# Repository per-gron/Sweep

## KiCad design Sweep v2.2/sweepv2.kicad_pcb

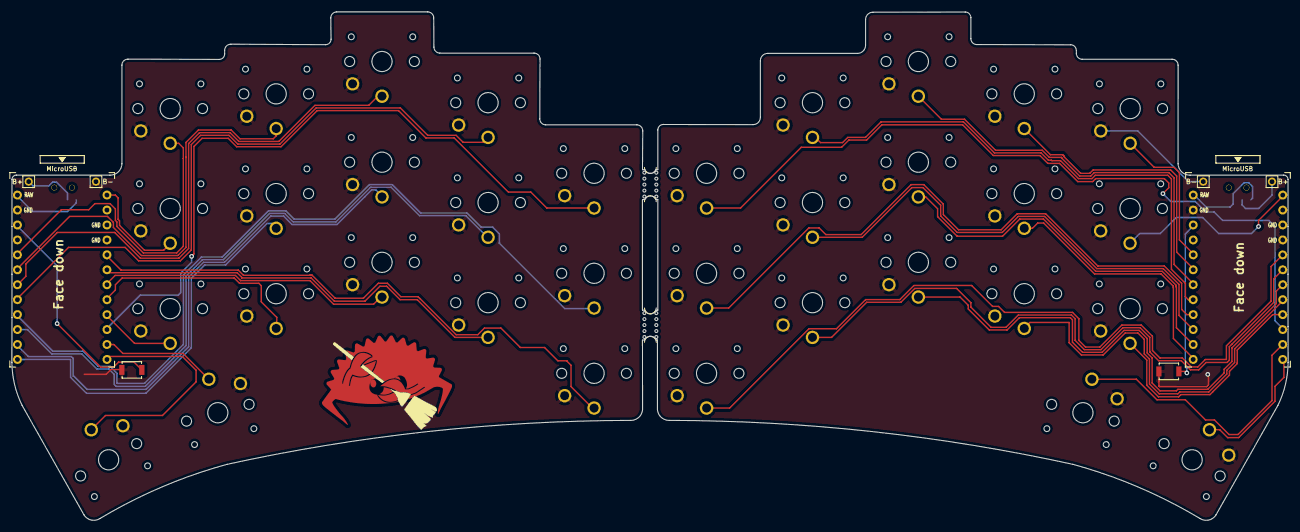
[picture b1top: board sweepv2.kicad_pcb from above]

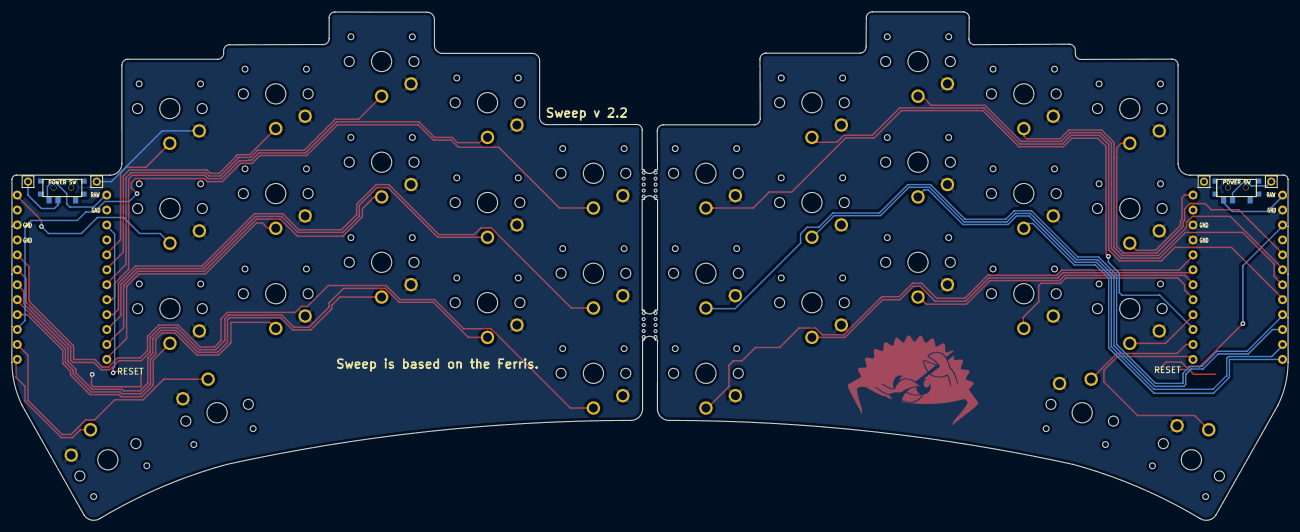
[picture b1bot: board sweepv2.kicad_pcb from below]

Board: 2 copper layers, 216.9 x 86.4 mm, 46 parts (2 on the bottom side), 41 nets.

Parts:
B+: MountingHole_Pad; 1pin_conn
B+#2: MountingHole_Pad; 1pin_conn
B-: MountingHole_Pad; 1pin_conn
B-#2: MountingHole_Pad; 1pin_conn
POWER SW: SW_SPDT; SPDT_C128955
POWER SW#2: SW_SPDT; SPDT_C128955
RSW1, RSW2: SW_Push; SW_SPST_B3U-1000P
SW2, SW2_r1, SW3, SW3_r1, SW4, SW4_r1, SW5, SW5_r1, SW6, SW6_r1, SW7_r1, SW8, SW8_r1, SW9, SW9_r1, SW10, SW11, SW11_r1, SW12, SW12_r1, SW13_r1, SW14, SW15, SW15_r1, SW16, SW16_r1, SW17, SW17_r1, SW18, SW18_r1, SW20, SW20_r1, SW21, SW21_r1: SW_Push; choc-v1-with-millmax
U1, U2: ProMicro-kbd; ProMicro_v3_min
mouse-bite-2mm-slot, mouse-bite-2mm-slot#2: VAL**; mouse-bite-5mm-slot-with-space-for-track

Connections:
BT+: B+#2.1, POWER SW#2.2
BT+_r: B+.1, POWER SW.2
Switch1: SW2.1, U1.10
Switch1_r: SW2_r1.1, U2.10
Switch2: SW3.1, U1.17
Switch2_r: SW3_r1.1, U2.17
Switch3: SW4.1, U1.18
Switch3_r: SW4_r1.1, U2.18
Switch4: SW5.1, U1.19
Switch4_r: SW5_r1.1, U2.19
Switch5: SW6.1, U1.20
Switch5_r: SW6_r1.1, U2.20
Switch6: SW8.1, U1.16
Switch6_r: SW7_r1.1, U2.16
Switch7: SW9.1, U1.15
Switch7_r: SW8_r1.1, U2.15
Switch8: SW10.1, U1.14
Switch8_r: SW9_r1.1, U2.14
Switch9: SW11.1, U1.13
Switch9_r: SW11_r1.1, U2.13
Switch10: SW12.1, U1.1
Switch10_r: SW12_r1.1, U2.1
Switch11: SW14.1, U1.5
Switch11_r: SW13_r1.1, U2.5
Switch12: SW15.1, U1.6
Switch12_r: SW18_r1.1, U2.6
Switch13: SW16.1, U1.7
Switch13_r: SW15_r1.1, U2.7
Switch14: SW17.1, U1.8
Switch14_r: SW16_r1.1, U2.8
Switch15: SW18.1, U1.9
Switch15_r: SW17_r1.1, U2.9
Switch16: SW21.1, U1.11
Switch16_r: SW21_r1.1, U2.11
Switch17: SW20.1, U1.12
Switch17_r: SW20_r1.1, U2.12
gnd: B-.1, B-#2.1, RSW1.1, RSW2.1, SW2.2, SW2_r1.2, SW3.2, SW3_r1.2, SW4.2, SW4_r1.2, SW5.2, SW5_r1.2, SW6.2, SW6_r1.2, SW7_r1.2, SW8.2, SW8_r1.2, SW9.2, SW9_r1.2, SW10.2, SW11.2, SW11_r1.2, SW12.2, SW12_r1.2, SW13_r1.2, SW14.2, SW15.2, SW15_r1.2, SW16.2, SW16_r1.2, SW17.2, SW17_r1.2, SW18.2, SW18_r1.2, SW20.2, SW20_r1.2, SW21.2, SW21_r1.2, U1.3, U1.4, U1.23, U2.3, U2.4, U2.23
raw: POWER SW.3, POWER SW#2.3, U1.24, U2.24
reset: RSW1.2, U1.22
reset_r: RSW2.2, U2.22
vcc: U1.21, U2.21

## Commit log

2023-02-25 Remove TRRS jacks
    They are not used with ZMK.
2023-02-25 Update board outline a little bit
2023-02-26 Remove the tilting puck holes and adjust the shape
